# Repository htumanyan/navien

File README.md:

# Navien ESPHome Integration 🚀🔥

Take control of your **Navien gas water heater** directly from Home
Assistant with this ESPHome module!

No more proprietary lock-ins - this project lets you seamlessly
integrate your Navien system into your smart home setup, giving you
automation superpowers like:

-   📱 Remote start/stop from Home Assistant
-   🔔 "Hot Button" entity that can be triggered from automation
-   ⚡ Climate control for setting the target temperature
-   🛠️ Easy to build, flash, and configure with YAML

## Screenshots 🖼️

Here are some examples of how the integration looks in Home Assistant:

This project grew out of my work on reverse engineering the native Navien communication protocol to automate my Navien 240a, which it is tested with thoroughly (and works in my home every day). It also incorporates the knowledge from work done by amazing folks in Home Assistant community: [tsquared](https://github.com/tsquared96), [https://github.com/Suva](https://github.com/Suva), [evanjarrett](https://github.com/evanjarrett), David Carson, smurf12345 and many others who contributed in the [community thread](https://community.home-assistant.io/t/navien-esp32-navilink-interface/720567/118)

👉 GitHub Repo: [htumanyan/navien](https://github.com/htumanyan/navien)

------------------------------------------------------------------------

## Getting Started 🛠️

Follow these steps to build and run your own Navien ESPHome integration.

### 1. Clone the Repository

```
git clone https://github.com/htumanyan/navien.git 
cd navien
```

### 2. Install ESPHome

If you don't already have ESPHome installed:

```
pip install esphome
```

For detailed installation instructions, see the [ESPHome Getting Started
guide](https://esphome.io/guides/getting_started_command_line.html).

### 3. Choose Your Configuration

There are five ready-to-use YAML configurations in this repo:

-   **navien-d1-mini.yml** → If you use the D1 Mini board
-   **navien-wrd-hb.yml** → Version for D1 Mini with a hardwired hot button simulator
-   **navien-esphome-atom-lite-esp32.yml** → If you use esp32 Atom Lite board
-   **navien-esphome-lolin-c3-mini.yml** → If you use a LOLIN/WEMOS C3 Mini board
-   **navien-ht-device.yml** → This is for custom esp device that I've designed and plan to open source soon

For ESPHome Dashboard's **Import from URL** workflow, use the LOLIN/WEMOS
C3 Mini package at
`github://htumanyan/navien/esphome/packages/navien-esphome-lolin-c3-mini.yaml@main`.

### 5. Configure Wi-Fi

```
cp secrets.yaml.sample secrets.yaml
```
Edit secrets.yaml - change XXXX to your Wi-Fi network/password and AP SSID network/password in case if it fails to acquire Wi-Fi connection

#### Optional: password-protect the web server

Most of the configs in this repo enable ESPHome's [web server](https://esphome.io/components/web_server.html) on port 80 without a password, so anyone on your network can open the heater's web UI and change its settings. To require a login, add these to `secrets.yaml`:

```yaml
esp_web_user: "XXXXXXXXXX"
esp_web_password: "XXXXXXXXXX"
```

Then add this to your device YAML, or uncomment the `auth:` block in `navien-transport-wifi.yml`:

```yaml
web_server:
  auth:
    username: !secret esp_web_user
    password: !secret esp_web_password
```

ESPHome merges this with the `web_server` settings from the package, so the port and other options stay the same. Home Assistant connects through the native API, not the web server, so it isn't affected.

### 6. Compile and Upload

Compile your firmware:

```
bash esphome compile navien-wrd-hb.yml 
```

**IMPORTANT: ensure that you are running the latest version of esphome, 2025.11.4 or later. Esphome introduced incompatible changes after the version 2025.7.4 that this repo was based off of. Hence it is critical to ensure the latest version of esphome is applied.**

Flash it to your ESP32:

```
bash esphome run navien-wrd-hb.yml
```

### 7. Hardware

#### [Hardware Build Guide — RS485 Adapter](./hardware-guide.md)

Complete guide covering the M5Stack AtomS3 Lite + Atomic RS485 Base build, connector pinouts, wiring, how to enable NaviLink in the Navien installer menu, and common mistakes.

#### [Navien-240 Connector Reference](./doc/240.md)

---

### 8. Importing the Scheduled Recirculation Automation Blueprint

If you have a unit, such as the NPE2 series, that supports scheduled recirculation (meaning it has recirculation modes named something like "Always", "Intelligent", "Weekly", etc), and setting your unit to one of those modes results in the "Navien Recirculation Mode" sensor in Home Assistant reporting "External Scheduled" or "Internal Scheduled", then you can likely use the automation blueprint for scheduling your unit's recirculation times. To do that:

First, you need to create a Schedule entity that will control when circulation is active:

1. In Home Assistant, go to "Settings", "Devices and Services"
2. Click "Add integration"
3. Find "Schedule (helper)" and select it
4. Give the schedule a name like "Navien Recirculation", and set up the schedule (or you can do that part later)
5. Click "Create"

Then, set up the automation:

1. In Home Assistant, go to "Settings", "Automations & scenes", then to the "Blueprints" tab.
2. Click "Import Blueprint" in the lower-right corner
3. Enter Blueprint address: `https://raw.githubusercontent.com/htumanyan/navien/refs/heads/main/navien_schedule_automation_blueprint.yaml`
4. Click "Preview", then "Import blueprint"
5. In the list of blueprints, "Navien Scheduled Recirculation" should now appear. Click it.
6. Fill in all the values per the directions (you might need to create some more helper entities depending on how you want to do things)
7. Click "Save" and give the new automation a name.

### 9. Command Mode (original NPE-A / NPE-S units)

Original NPE-A/NPE-S units (for example an NPE-240A, reported as device type `NPE`) ignore the
"Allow Recirculation" **on** command, the DHW setpoint and the power on/off commands as the
component has always sent them. A real NaviLink talks to these units differently: it only transmits
when the bus is idle, announces itself every few seconds instead of after every packet, and sends
every control command with a token byte (byte 12), repeated, followed by an all-zero control packet
carrying the same token. The `command_mode` option selects which behaviour is used:

```yaml
sensor:
  - platform: navien
    id: navien_main
    command_mode: auto      # auto (default) | legacy | navilink
```

- `auto` (default): `navilink` handling when the unit reports device type `NPE`, `legacy` for
  everything else (NPE2, NCB, NCB-H, ...), so existing installs keep their current behaviour.
- `legacy`: the original behaviour.
- `navilink`: always use the NaviLink-style handling.

In `navilink` mode the component also confirms recirculation changes against the unit's reported
state and resends up to 3 times if the unit did not take the command.

Note: in °F mode an NPE-A only accepts the setpoints its front panel offers (5 °F steps above
120 °F, e.g. 125/130/135/140); other values are silently ignored by the unit. The diagnostic
`Command Mode` text sensor (`command_mode_status`) shows which mode is active.

### 📖 User Manual for Custom Navien Controller

For detailed instructions on connecting, configuring, and using the custom Navien controller device, see the [User Manual](./doc/user_manual.md). This guide covers hardware setup, wiring, and usage tips specific to the custom controller.

------------------------------------------------------------------------

## [Protocol Details](./doc/README.md) 🔬

If you're interested in how this integration works under the hood, check
out the [doc](./doc/README.md) subfolder.
It contains the **reverse-engineered details of the Navien
protocol**---including message formats, field definitions, and notes
from packet captures.

This section is for developers and contributors who want to:
- Understand the low-level communication between the ESP32 and Navien
heater
- Contribute improvements to the protocol implementation
- Extend support for additional Navien models or features

If you just want to use the integration, you don't need to worry about
this --- but if you love digging into protocols, that's where the magic
happens.

------------------------------------------------------------------------

## Next Steps 🌟

-   Add your device to **Home Assistant** using ESPHome integration.
-   Create **automations and dashboards** to trigger hot water
    recirculation with a tap, schedule, or voice assistant.
-   Share your setup and feedback with the community!

------------------------------------------------------------------------

💡 This project is community-driven. Contributions, pull requests, and
feature ideas are always welcome!

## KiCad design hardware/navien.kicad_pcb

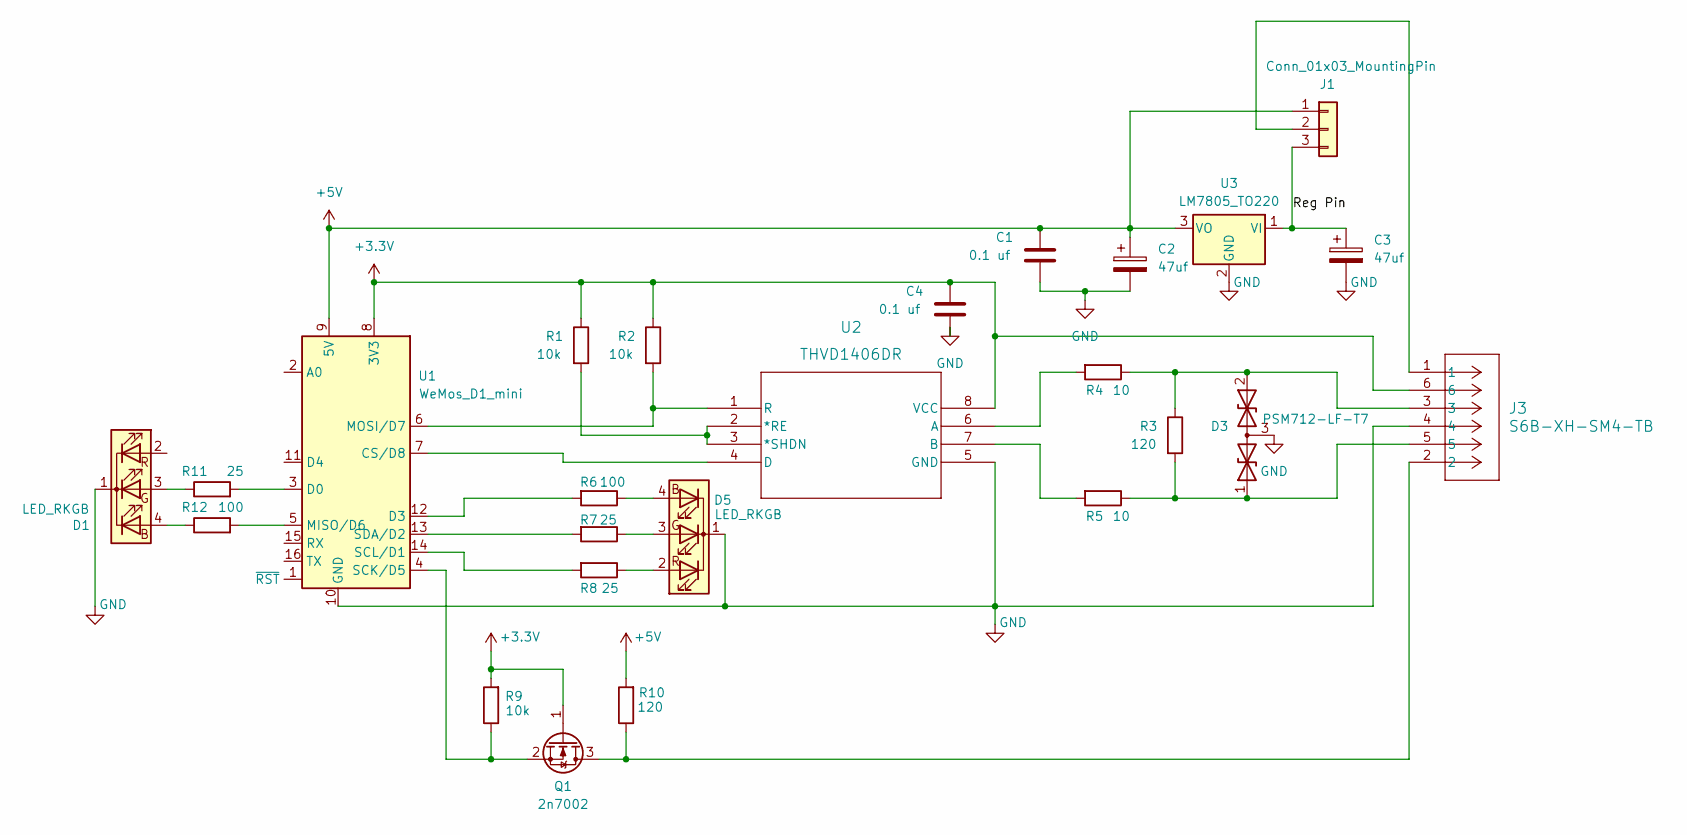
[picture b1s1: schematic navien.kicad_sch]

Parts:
C1, C4: 0.1 uf; C_0805_2012Metric_Pad1.18x1.45mm_HandSolder
C2, C3: 47uf; CP_EIA-3216-18_Kemet-A_Pad1.58x1.35mm_HandSolder
D1, D5: LED_RKGB; LED-ARRAY-SMD_4P-L1.6-W1.5-BL-FD
D3: PSM712-LF-T7; SOT-23
J1: Conn_01x03_MountingPin; PinHeader_1x03_P2.54mm_Vertical
J3: S6B-XH-SM4-TB; CONN_S6B-XH-SM4-TB_JST
Q1: 2n7002; SOT-23
R1, R2, R9: 10k; R_0805_2012Metric_Pad1.20x1.40mm_HandSolder
R3, R10: 120; R_0805_2012Metric_Pad1.20x1.40mm_HandSolder
R4, R5: 10; R_0805_2012Metric_Pad1.20x1.40mm_HandSolder
R6, R12: 100; R_0805_2012Metric_Pad1.20x1.40mm_HandSolder
R7, R8, R11: 25; R_0805_2012Metric_Pad1.20x1.40mm_HandSolder
U1: WeMos_D1_mini; WEMOS_D1_mini_light
U2: THVD1406DR; SOIC_D0008A_TEX
U3: LM7805_TO220; TO-220-3_Vertical

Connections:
+3.3V: C4.1, J3.6, Q1.1 (G), R1.1, R2.1, R9.2, U1.8 (3V3), U2.8 (VCC)
+5V: C1.1, C2.1, J1.1, R10.2, U1.9 (5V), U3.3 (VO)
/Reg Pin: C3.1, J1.3, U3.1 (VI)
GND: C1.2, C2.2, C3.2, C4.2, D1.1 (RA), D3.3 (common), D5.1 (Cathode), J3.4, U1.10 (GND), U2.5 (GND), U3.2 (GND)
unnamed: D1.3 (G), R11.1
unnamed: D1.4 (R), R12.1
unnamed: D3.1 (A1), J3.5, R3.2, R5.1
unnamed: D3.2 (A2), J3.3, R3.1, R4.1
unnamed: D5.2 (B), R8.1
unnamed: D5.3 (G), R7.1
unnamed: D5.4 (R), R6.1
unnamed: J1.2, J3.1
unnamed 12: R2.2, U1.6 (MOSI/D7), U2.1 (R); also elsewhere on the board
unnamed 13: U1.7 (CS/D8), U2.4 (D); also elsewhere on the board
unnamed: J3.2, Q1.3 (D), R10.1
unnamed: Q1.2 (S), R9.1, U1.4 (SCK/D5)
unnamed: R11.2, U1.3 (D0)
unnamed: R6.2, U1.12 (D3)
unnamed: R12.2, U1.5 (MISO/D6)
unnamed: R8.2, U1.14 (SCL/D1)
unnamed: R7.2, U1.13 (SDA/D2)
unnamed: R1.2, U2.2 (*RE), U2.3 (*SHDN)
unnamed: R4.2, U2.6 (A)
unnamed: R5.2, U2.7 (B)

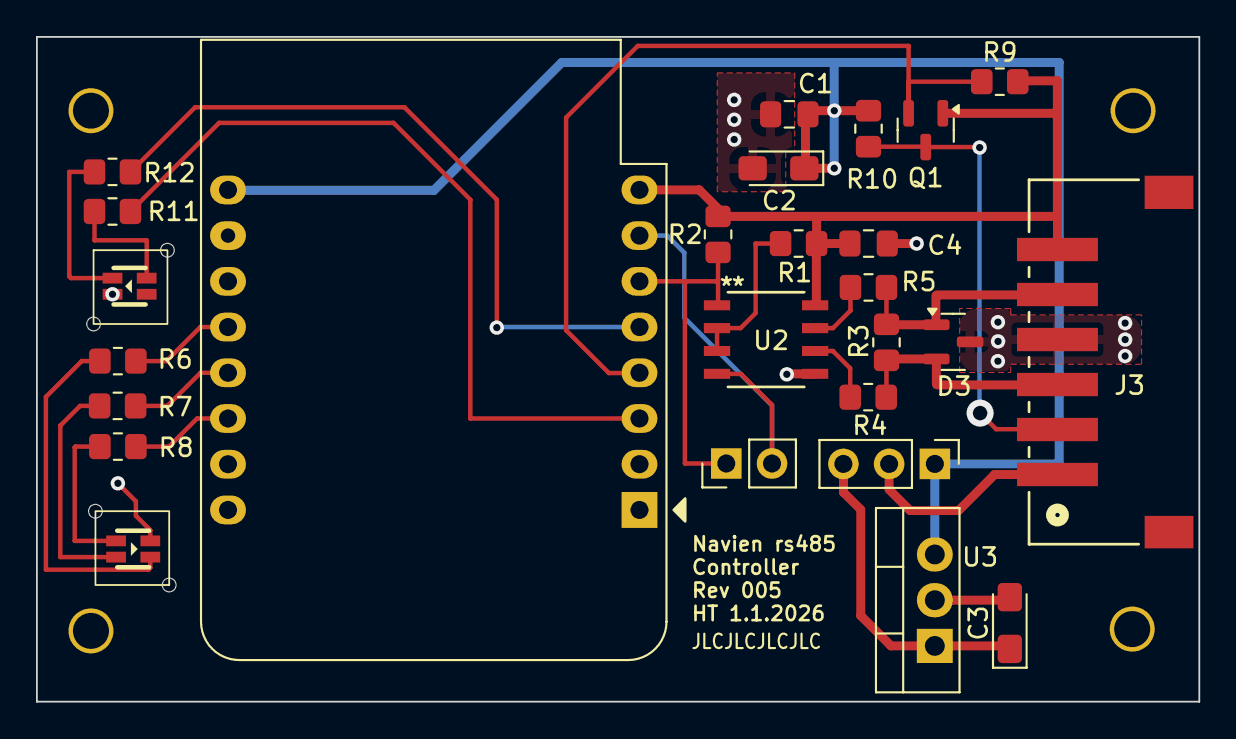
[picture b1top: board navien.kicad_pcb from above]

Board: 2 copper layers, 64.6 x 36.9 mm, 30 parts (0 on the bottom side), 24 nets.

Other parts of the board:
J2: Conn_01x02; PinHeader_1x02_P2.54mm_Vertical
REF1, REF2, REF3, REF4: MountingHole_2.2mm_M2

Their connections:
unnamed 12: J2.1; also elsewhere on the board
unnamed 13: J2.2; also elsewhere on the board

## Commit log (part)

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2024-03-10 Initial blurb
2024-03-10 Tweak the title
2024-03-23 Added separate page for rs485 proto and also descriptions of packet format and header
2024-04-06 Added Saleae Logic 2 trace files
2024-08-27 Added detailed documentation on the checksum
2024-08-27 Removed the unnecessry comments
2025-01-04 Added support for external secrets file Rename secrets.yaml sample into secrets.yaml and change XXXX to repsective ap name and password values
2025-01-04 Initial checking of payload details - differentiation between status and control as well as basic details on gas/water payload distinction
2025-01-05 Added a link to esphome sources
2025-01-05 Added the link to payload documentation
2025-02-01 Fixed the image link
2025-02-03 Reworked the component structure for better alignment with esphome best practices Added Navien Switch for turning the heater on/off (tested to work with N240a)
2025-02-19 Update navien_wifi_debug.md
    Fixed a typo
2025-06-15 Fixed the compilation error due to incorrectly added button Added NavienOnOff switch for tracking the state of the device and also turning it on and off Added reporting of the water flow state
2025-06-21 Update my branch for the newly merged changes.
2025-06-21 Convert Navien from a PollingComponent to a plain Component. This results in the sensor data being published as it comes in on the serial port rather than every 5s.
2025-06-22 Use templated sensors in order to only publish to Home Assistant every 5s.
2025-06-22 Update to match both the upstream changes and my changes to its parent branch "refactor/4-remove-polling".
2025-06-24 Major refactoring to achieve greater flexibility: a. Created a new interface abstracting away the details of UART and modified the rest of the code to use that rather than the raw esphome UART API. b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
2025-06-25 Removed unnecessary parse_gas and parse_water that are now replaced with calls to on_gas and on_water in the implementation of NavienLinkVisitorI. Moved the code from parse_gas and parse_water to the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
2025-06-25 Added the missing file modification to support accumulated gas usage
2025-06-25 Fixed the incorrect position of water flow field and confirmed correct GPM reporting on the actual unit
2025-06-26 a. Fixed the bug in water flow calculation - was mistakenly treating the value as GPM while it was LPM b. Added the current gas consumption - it is reported in kkal/hr but shown as BTU in Navien. Imp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
2025-06-29 Added the water utilization (debugged to confirm proper functioning) Replaced the use of module-specific unit of m^3 with ESPHome standard
2025-06-29 Fixed the power on/off. Debugged and verified it is working Moved sensor updates into their own functions update_water_sensors and update_gas sensors so that we could call them either from the Pollin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
2025-07-08 Fixed a bug in send command queueing - the buffer was not duplicated, which could have caused issues if the sender code modified the buffer it supplied before the actual serialization to rs485 line c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
2025-08-25 Split off the configuration into separate files to simplify building for various platforms.
    navien-wrd-hb.yml - for the option that has D5 pin connected to the hot button pin on Navien main board (hot button simulation)
    navien-ht-device.yml - for the custom device that was designed specifically for controlling Navien devices.
    navien-base.yml - base file re-used across all versions, contains common definitions
    navien.yml is still around but will be retired soon
2025-09-06 Updated the navien.yaml for the new structure of platofrm/board specification in the latest version of esphome
2025-09-06 Fixed reading temp values from water packet (was missing proper conversion to temp units). Added support for modes - HEAT and OFF. Wired up the modes to the on/off state of the Navien unit. Turning o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
2025-09-06 Rearranged the documentation and added build instructions for esphome
2025-09-06 Removed the 2-wire link
2025-09-06 Added the missing step of secrets.yaml configuration
2025-09-08 Removed unnecessary port manipulations. Added the thermostat (missed when thermostat support was developed)
2025-09-09 Enable hot button
2025-09-09 Add esphome configs
2025-09-09 Update CONF_GAS_TOTAL with device and state classes
    Allows sensor to be used in the energy dashboard
2025-09-09 Simplify gas_total
    Filter, unit)of_measurement and accuracy are no longer needed with
    device and state class being set. These can now be specified in the Home
    Assistant UI.
2025-09-26 Enable hot button and addition of default sensor icons
2025-09-26 Tweaks to make it work with the shared navien-base.yml
2025-10-04 Made changes to allow remote build with HA esphome dashboard Refer to navien.example.yml on how to to that
2025-10-07 Fixed the git import path - was quitely failing to pull dependency files from git, causing misleading error messages
2025-10-09 Added the hardware KiCad project with schematic and PCB Added the PNG verison of schematic for easy preview
2025-11-28 Add cubic feet gas sensor and adjust water flow unit
2025-11-28 Enable real-time Navien sensor updates in examples
2025-11-28 Add device classes and update gas usage units
2025-11-29 Add Navien system status and heating temp sensors
2025-11-29 Made LED lights come on/off based on Wi-Fi and RS-485 connection status
2025-12-02 Use volume_flow_rate device class for water flow sensor
2025-12-05 Added missing sensor definitions Tested successful compile but not operation
2025-12-06 Switch to use of add_feature_flags() in climate traits
2025-12-07 Highlight esphome version requirement
    Added a note about the importance of using the latest version of esphome.
2025-12-12 Update README to include community contributions
    Expanded project description to acknowledge contributions from the Home Assistant community.
2025-12-30 Temporary re-adddition of the soft rs485 button while figuring out a way to have both options
2026-01-07 doc: consolidate Navien 240 documentation (240A/240A2): add doc/240.md, update README, remove doc/240-a.md
2026-01-08 docs(user_manual): use markdown table for side-by-side 240A/240A2 images
2026-01-09 Fleshed out features and parameters for NCB-H combi model.
2026-01-09 Enable raw packet trace print (uncomment print_buffer in navien_link.cpp)
2026-01-10 -Added support for NCB240/130H combi-boiler -Decoded several other additional parameters
2026-01-11 Slight refactoring for better code organization.
2026-01-11 Added more logging to trace hot button press. Also modified the protocol parser to ignore the slave unit for now so that we can verify the proper functioning of the master
2026-01-12 Trace logs when dequeued commands are sent over UART (print buffer + length)
2026-01-13 Update navien climate component for ESPHome 2025 compatibility
2026-01-15 Phase 1 of refactoring to support multi-unit cascading setup. Modified the reception logic to decide on packet direction based on the direction field, modified the navien_link to pass along src id of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
2026-01-15 Add inlet and outlet temperature sensors for slave unit
2026-01-17 Added test vectors from the slave unit collected in 240A2 cascade setup and modified the packet validatio to use proper seed values.
2026-01-17 disabled parsing of control packets with the source other than 0xF as those are unknown at the moment (observed in cascade setup for 240A2 between navien units) and cause unnecessary errors.
2026-01-18 Renamed _slave and _master to _sub and _main to match Navien terminology
2026-01-18 Remove temporary print/trace statements from sensor.py
2026-01-20 Fix Fahrenheit rounding issues
2026-01-20 Disable inlet temp realtime updates
2026-01-20 Default inlet temp realtime to off
2026-01-20 Gate inlet temp publish during realtime updates
2026-01-21 Add support for m5Stack ATOM S3 Lite/Tail485
    Adds a configuration file for the ATOM S3 Lite with a Tail485, which uses a different pinout than the ATOM S3.
    Also adds info to `doc/240.md` about pin mapping between the 5-pin connector 1 and the NaviLink RJ45 cable.
2026-01-26 Use idf for atom-lite
    Also resolve an issue with the `/` character in the name of the power
    entity
2026-01-26 Resolve warning about deprecated method
2026-02-04 bitmask fixes
2026-02-08 Add ESPHome 2026.1 support and agent instructions
2026-02-10 Remove VS Code workspace files and ignore
2026-02-10 Remove unused navien_link component copy
2026-02-17 Support configuration without switch or climate components
    Add USE_SWITCH/USE_CLIMATE guards around usage areas and minor
    refactoring to eliminate duplication.
2026-02-17 Move controller_version_hi and panel_version_hi fields back to unknown
    And remove _lo from remaining associated fields.
    Since the refactor last month in 04631a8, the _hi portions are
    unreferenced and do not contribute to decoded version strings.
2026-02-17 Add support for space heating set temperature
    The value comes from gas packet field index 13, previously known as
    panel_version_hi.
    Confirmed by observing NFC-250/175H unit.
2026-02-21 Fix error handling and src
    Changes where on_error() is called from so it's only called for actual errors, not whenever there's no command to send (fix migrated from #41 since this PR doesn't work well without it).
    Also added a guard in loop() to only call receive() if the Navien object is the primary instance, to prevent extra receive() calls in a cascaded setup.
2026-02-21 Add the Atom S3 Lite config to build.py
2026-02-22 Handle configuration without all sensors defined in on_error
    And reset state for all currently sensors.
2026-02-22 Add decoding and sensors for outdoor temperature
    Gas packet byte 19 observed on NCB and NFC models.
2026-02-28 Extract climate config to dedicated file, add water heater example.
    Climate still included by default so should be no change for any
    existing remote includes.
    Leave water heater off by default as no convenient way to make
    configurable without requiring esphome >= 2025.12.0.
2026-03-27 Fix icon codegen for ESPHome 2026 APIs
2026-03-27 Remove deprecated climate current-temperature trait call
2026-03-27 Fix cascade status routing by source address
2026-03-29 Add HA-compatible gas sensors (CCF, kW) alongside legacy Therms/BTU sensors
    Instead of replacing the existing Therms and BTU sensors (which match the
    Navilink app), preserve them for backward compatibility and add new
    HA-standards-compliant sensors as disabled-by-default copy sensors.
    - "Therms" is not a valid HA unit for device_class "gas", causing warnings:
    "Entity sensor.navien_accumulated_gas_usage is using native unit of
    measurement 'Therms' which is not a valid unit for the device class ('gas')"
2026-04-09 Add water heater config example, commented out by default.
2026-04-10 Add decoding and sensors for error code and level
2026-04-10 navien: avoid explicit std::optional in climate control
2026-04-11 test: disable gas-path publishing to isolate temp oscillation
2026-04-18 Reworked command-sending to handle acknowledgement
    While observing the behavior of an actual NaviLink Lite connected to my NPE-240A2, I discovered two things about its behavior:
    1. The command packet `HOT_BUTTON_RELSE_CMD` is actually sent after every command, not just after the Hot Button command.
    2. The repeating of commands isn't arbitrary or a certain count. The NaviLink repeats the command until it sees a status packet that shows that the command took effect, and then when it does see that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
    This change implements this behavior. The `HOT_BUTTON_RELSE_CMD` packet has been renamed to `ACKNOWLEDGEMENT`, and each command packet that can
2026-04-29 Handle cascade sub-unit data frames from the master
